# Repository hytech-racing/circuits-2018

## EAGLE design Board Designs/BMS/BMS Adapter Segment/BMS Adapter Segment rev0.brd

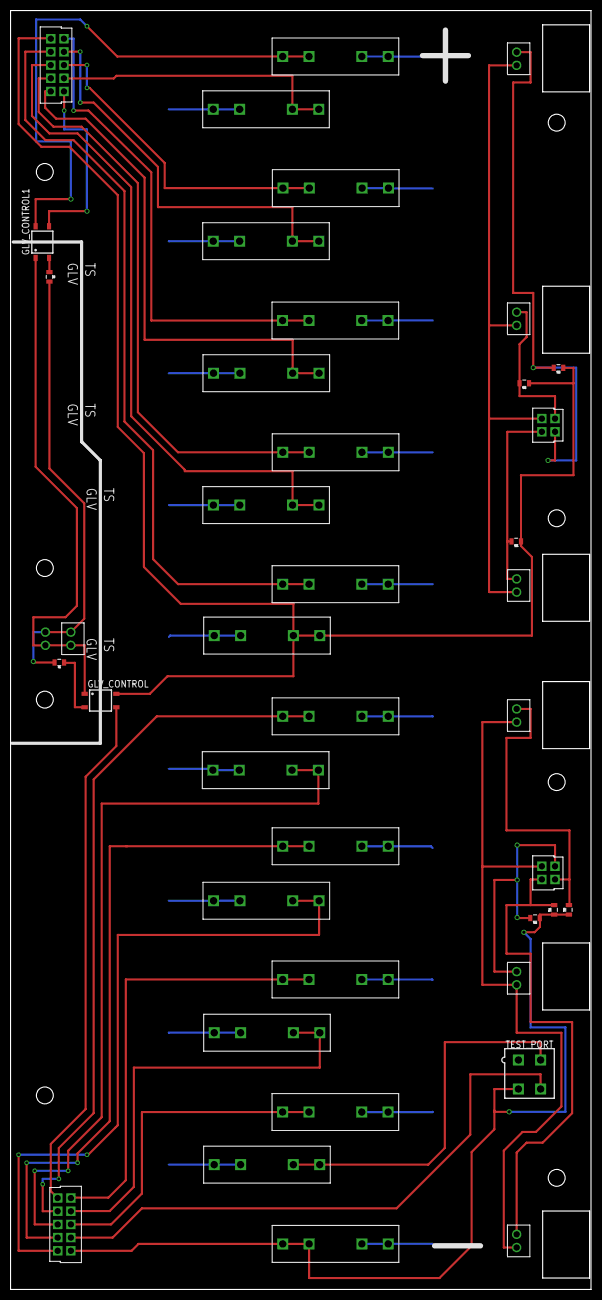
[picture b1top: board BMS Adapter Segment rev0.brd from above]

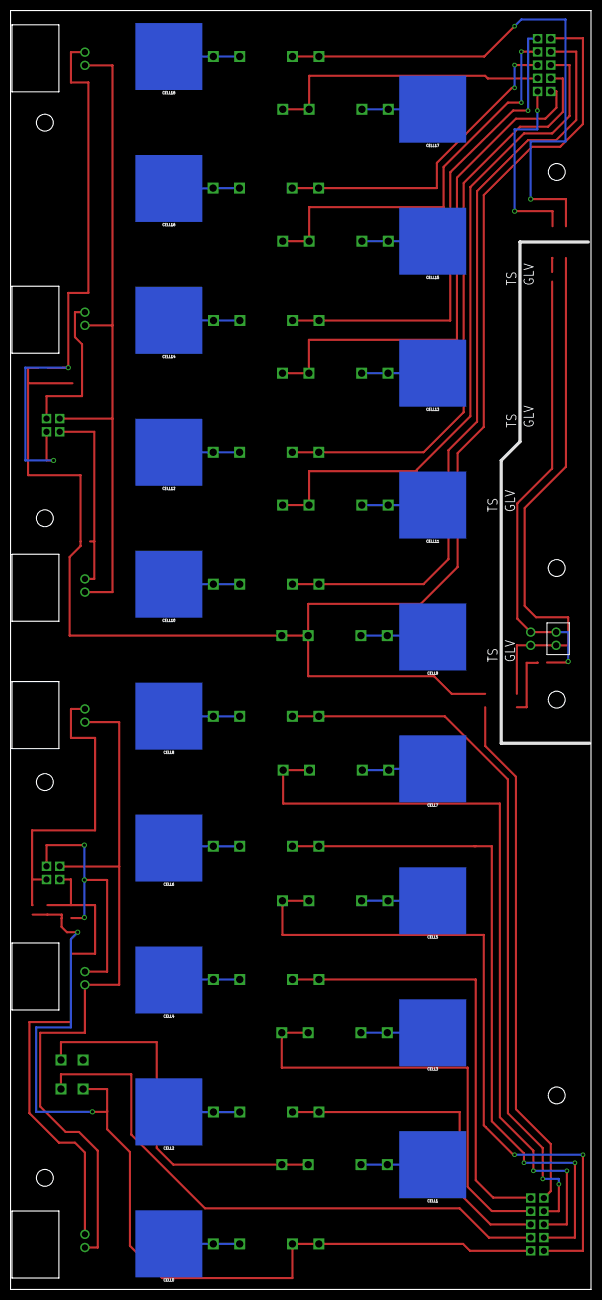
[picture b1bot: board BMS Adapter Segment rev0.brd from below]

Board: 2 copper layers, 110.0 x 242.4 mm, 61 parts (20 on the bottom side), 53 nets.

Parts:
CELL0, CELL1, CELL2, CELL3, CELL4, CELL5, CELL6, CELL7, CELL8, CELL9, CELL10, CELL11, CELL12, CELL13, CELL14, CELL15, CELL16, CELL17, CELL18: KEYSTONE5222
F0, F1, F2, F3, F4, F5, F6, F7, F8, F9, F10, F11, F12, F13, F14, F15, F16, F17, F18: 0751.0110
G1, G2: 2k; 0805
GLV_CONTROL, GLV_CONTROL1: CPC1002N; SOP04
TEST_PORT: MINIFIT_5566-4
TR1, TR2, TR3, TR4, TR5, TR6: 10kΩ; 0805
X1, X13: CONNECTOR-10NANO-FIT_VERTICAL_NO_CLIPS-10; NANO-FIT_VERTICAL_NO_CLIPS-10
X2, X3, X7, X8, X9, X10, X11, X12: CONNECTOR-2NANO-FIT_VERTICAL_NO_CLIPS-2; NANO-FIT_VERTICAL_NO_CLIPS-2
X5, X6: CONNECTOR-4NANO-FIT_VERTICAL_NO_CLIPS-4; NANO-FIT_VERTICAL_NO_CLIPS-4

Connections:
CC0: CELL0.P$1, F0.L1, F0.L2
CC1: CELL1.P$1, F1.L1, F1.L2
CC2: CELL2.P$1, F2.L1, F2.L2
CC3: CELL3.P$1, F3.L1, F3.L2
CC4: CELL4.P$1, F4.L1, F4.L2
CC5: CELL5.P$1, F5.L1, F5.L2
CC6: CELL6.P$1, F6.L1, F6.L2
CC7: CELL7.P$1, F7.L1, F7.L2
CC8: CELL8.P$1, F8.L1, F8.L2
CC9: CELL9.P$1, F9.L1, F9.L2
CC10: CELL10.P$1, F10.L1, F10.L2
CC11: CELL11.P$1, F11.L1, F11.L2
CC12: CELL12.P$1, F12.L1, F12.L2
CC13: CELL13.P$1, F13.L1, F13.L2
CC14: CELL14.P$1, F14.L1, F14.L2
CC15: CELL15.P$1, F15.L1, F15.L2
CC16: CELL16.P$1, F16.L1, F16.L2
CC17: CELL17.P$1, F17.L1, F17.L2
CC18: CELL18.P$1, F18.L1, F18.L2
GND: G1.2, G2.2, X2.P$2, X3.P$2
unnamed: GLV_CONTROL1.3, X1.P$10
unnamed: GLV_CONTROL.3, X13.P$10
SENSE0: F0.R1, F0.R2, TEST_PORT.3, TR1.1, TR2.1, TR3.1, X13.P$1
SENSE1: F1.R1, F1.R2, TEST_PORT.2
SENSE1_J: TEST_PORT.4, X13.P$2
SENSE2: F2.R1, F2.R2, X13.P$3
SENSE3: F3.R1, F3.R2, X13.P$4
SENSE4: F4.R1, F4.R2, X13.P$5
SENSE5: F5.R1, F5.R2, X13.P$6
SENSE6: F6.R1, F6.R2, X13.P$7
SENSE7: F7.R1, F7.R2, X13.P$8
SENSE8: F8.R1, F8.R2, X13.P$9
SENSE9: F9.R1, F9.R2, GLV_CONTROL.4, TR4.1, TR5.1, TR6.1, X1.P$1
SENSE10: F10.R1, F10.R2, X1.P$2
SENSE11: F11.R1, F11.R2, X1.P$3
SENSE12: F12.R1, F12.R2, X1.P$4
SENSE13: F13.R1, F13.R2, X1.P$5
SENSE14: F14.R1, F14.R2, X1.P$6
SENSE15: F15.R1, F15.R2, X1.P$7
SENSE16: F16.R1, F16.R2, X1.P$8
SENSE17: F17.R1, F17.R2, X1.P$9
SENSE18: F18.R1, F18.R2, GLV_CONTROL1.4
SSR-: G1.1, GLV_CONTROL.2
SSR-1: G2.1, GLV_CONTROL1.2
THERM1: TR1.2, X6.P$2, X7.P$2
THERM2: TR2.2, X6.P$3, X8.P$2
THERM3: TR3.2, X6.P$4, X9.P$2
THERM4: TR4.2, X5.P$2, X10.P$2
THERM5: TR5.2, X5.P$3, X11.P$2
THERM6: TR6.2, X5.P$4, X12.P$2
THERM_POWER_1: X6.P$1, X7.P$1, X8.P$1, X9.P$1
THERM_POWER_2: X5.P$1, X10.P$1, X11.P$1, X12.P$1
VCCINT: GLV_CONTROL.1, GLV_CONTROL1.1, X2.P$1, X3.P$1

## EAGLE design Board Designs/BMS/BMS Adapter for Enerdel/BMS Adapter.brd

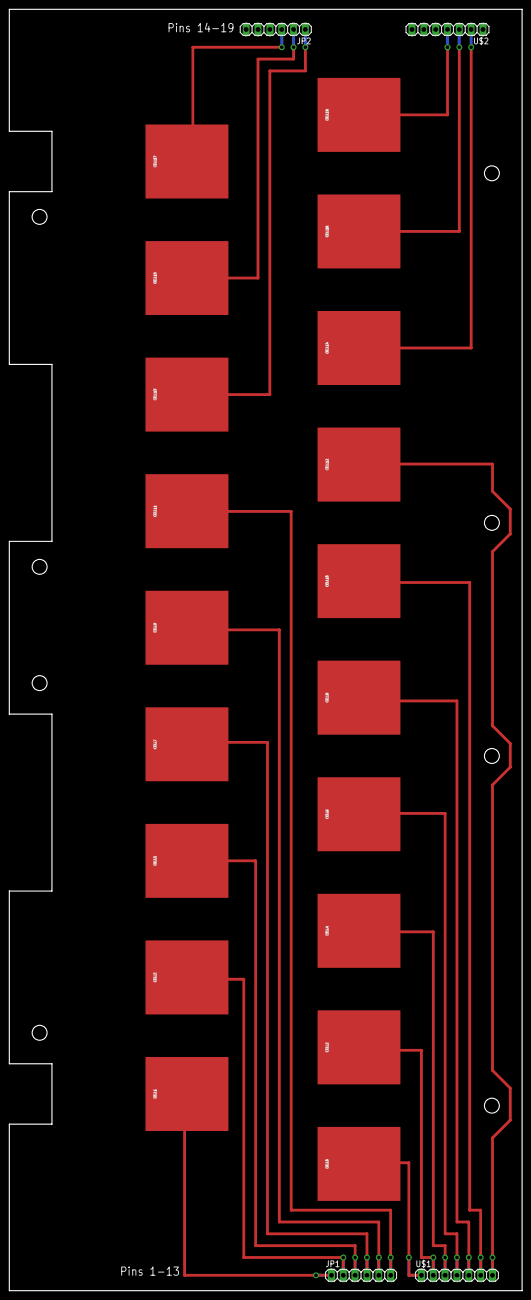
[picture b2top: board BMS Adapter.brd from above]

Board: 2 copper layers, 110.0 x 274.8 mm, 23 parts (0 on the bottom side), 19 nets.

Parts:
CELL0, CELL1, CELL2, CELL3, CELL4, CELL5, CELL6, CELL7, CELL8, CELL9, CELL10, CELL11, CELL12, CELL13, CELL14, CELL15, CELL16, CELL17, CELL18: BATTERY_SPRING_KEYSTONE5222; KEYSTONE5222
JP1, JP2: 1X06
U$1, U$2: M07; 1X07

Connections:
unnamed: CELL0.P$1, U$1.1
unnamed: CELL2.P$1, U$1.2
unnamed: CELL4.P$1, U$1.3
unnamed: CELL6.P$1, U$1.4
unnamed: CELL8.P$1, U$1.5
unnamed: CELL10.P$1, U$1.6
unnamed: CELL12.P$1, U$1.7
unnamed: CELL1.P$1, JP1.1
unnamed: CELL3.P$1, JP1.2
unnamed: CELL5.P$1, JP1.3
unnamed: CELL7.P$1, JP1.4
unnamed: CELL9.P$1, JP1.5
unnamed: CELL11.P$1, JP1.6
unnamed: CELL18.P$1, U$2.4
unnamed: CELL16.P$1, U$2.3
unnamed: CELL14.P$1, U$2.2
unnamed: CELL13.P$1, JP2.1
unnamed: CELL15.P$1, JP2.2
unnamed: CELL17.P$1, JP2.3

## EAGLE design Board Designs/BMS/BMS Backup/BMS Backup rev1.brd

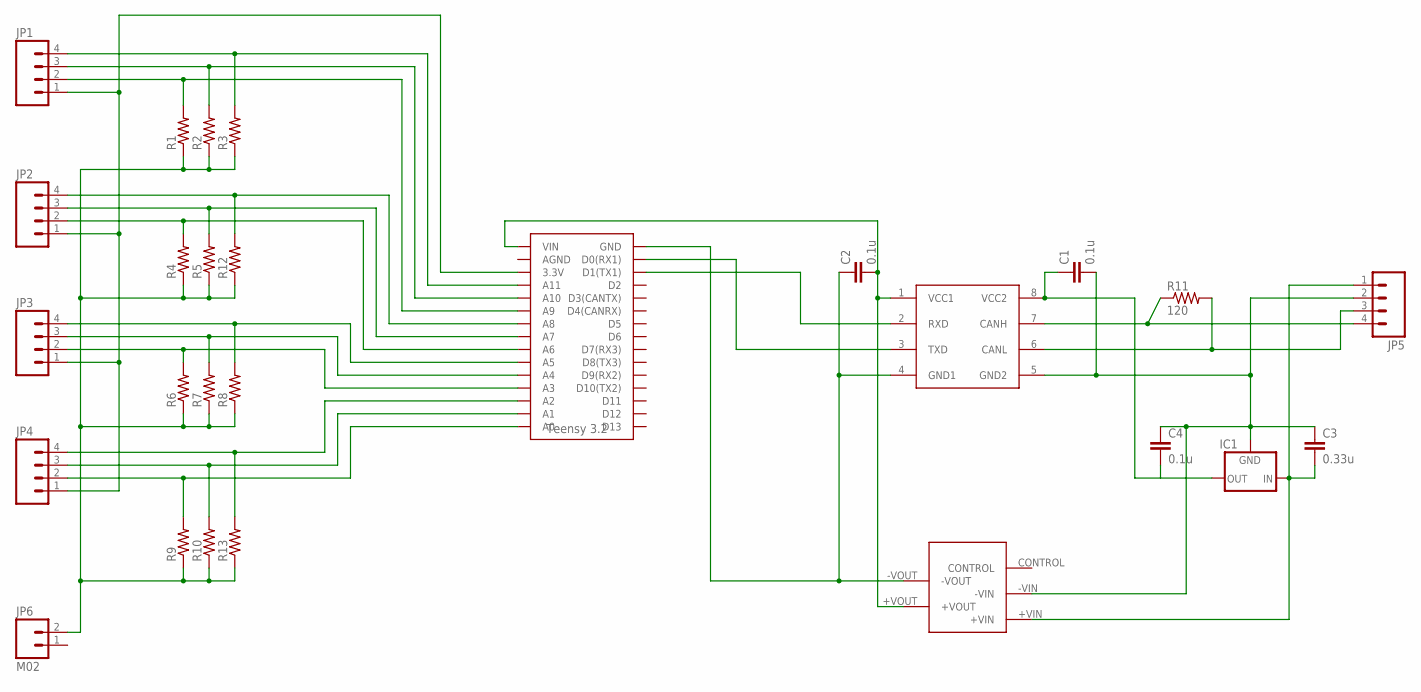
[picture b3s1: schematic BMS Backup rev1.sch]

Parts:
C1, C2, C4: 0.1u; 0805
C3: 0.33u; 0805
IC1: 5VREG_L7805SPACED; TO-220-SPACED
JP1, JP2, JP3, JP4, JP5: M04; 1X04
JP6: M02; 1X02
R1, R2, R3, R4, R5, R6, R7, R8, R9, R10, R12, R13: RESISTOR0805-RES; 0805
R11: 120; 0805
U$1: TEENSY_3.2_12ANALOG
U$2: ISO1050CAN; SOIC-08
U$3: NCS1S1205SC-12V-5VCONVERTER; DCDC-CONVERTER

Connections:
3.3V: JP1.1, JP2.1, JP3.1, JP4.1, U$1.3.3V
unnamed: C1.2, C3.1, C4.1, IC1.2 (GND), JP5.2, U$2.5 (GND2), U$3.-VIN
unnamed: JP3.3, R7.2, U$1.A4
unnamed: JP3.4, R8.2, U$1.A5
unnamed: C3.2, IC1.1 (IN), JP5.1, U$3.+VIN
unnamed: C1.1, C4.2, IC1.3 (OUT), U$2.8 (VCC2)
unnamed: JP5.4, R11.1, U$2.7 (CANH)
unnamed: JP5.3, R11.2, U$2.6 (CANL)
unnamed: U$1.D0(RX1), U$2.3 (TXD)
unnamed: U$1.D1(TX1), U$2.2 (RXD)
unnamed: C2.2, U$1.VIN, U$2.1 (VCC1), U$3.+VOUT
unnamed: C2.1, U$1.GND, U$2.4 (GND1), U$3.-VOUT
unnamed: JP2.4, R12.2, U$1.A8
unnamed: JP4.4, R13.2, U$1.A2
THERM1: JP1.2, R1.2, U$1.A9
THERM2: JP1.3, R2.2, U$1.A10
THERM3: JP1.4, R3.2, U$1.A11
THERM4: JP2.2, R4.2, U$1.A6
THERM5: JP2.3, R5.2, U$1.A7
THERM6: JP3.2, R6.2, U$1.A3
THERM9: JP4.2, R9.2, U$1.A0
THERM10: JP4.3, R10.2, U$1.A1
TS_GND: JP6.2, R1.1, R2.1, R3.1, R4.1, R5.1, R6.1, R7.1, R8.1, R9.1, R10.1, R12.1, R13.1

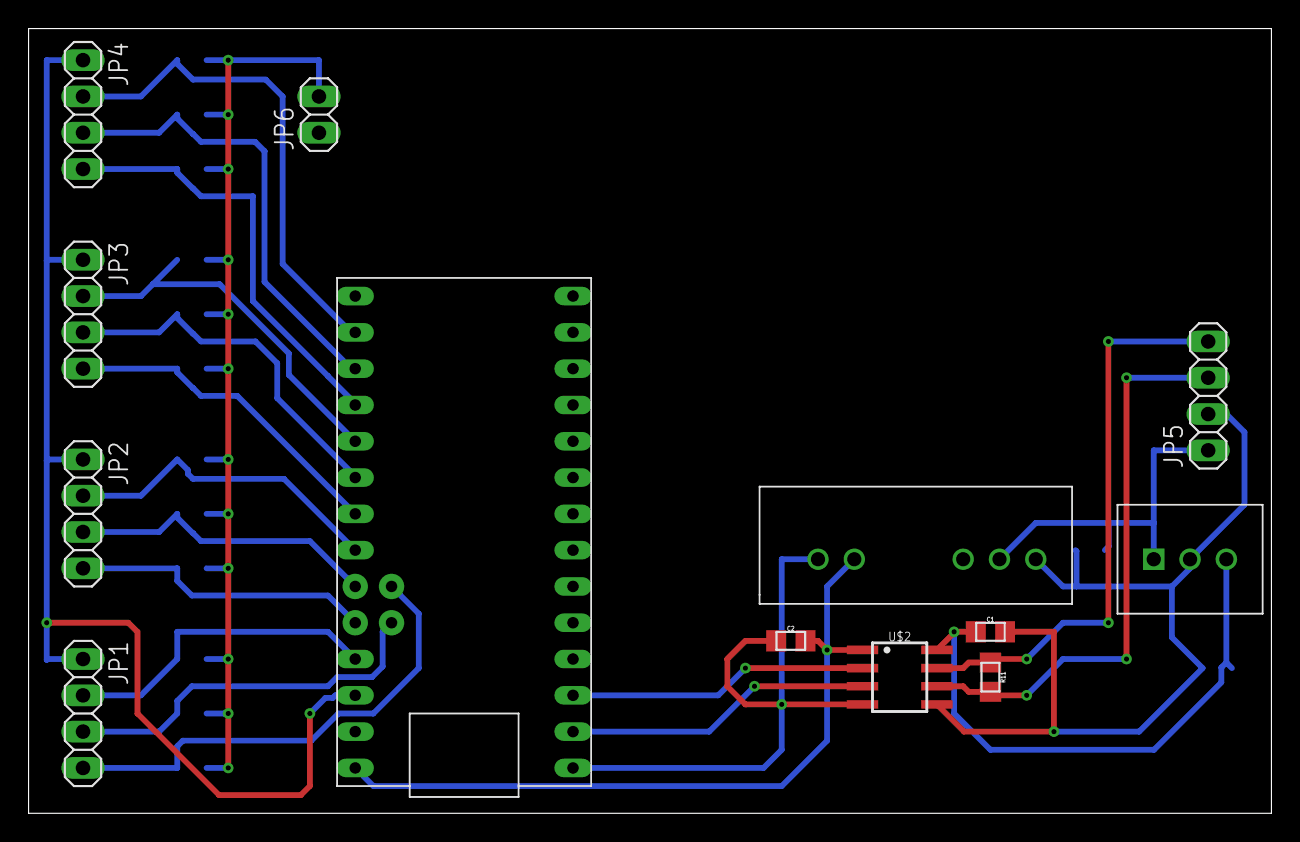
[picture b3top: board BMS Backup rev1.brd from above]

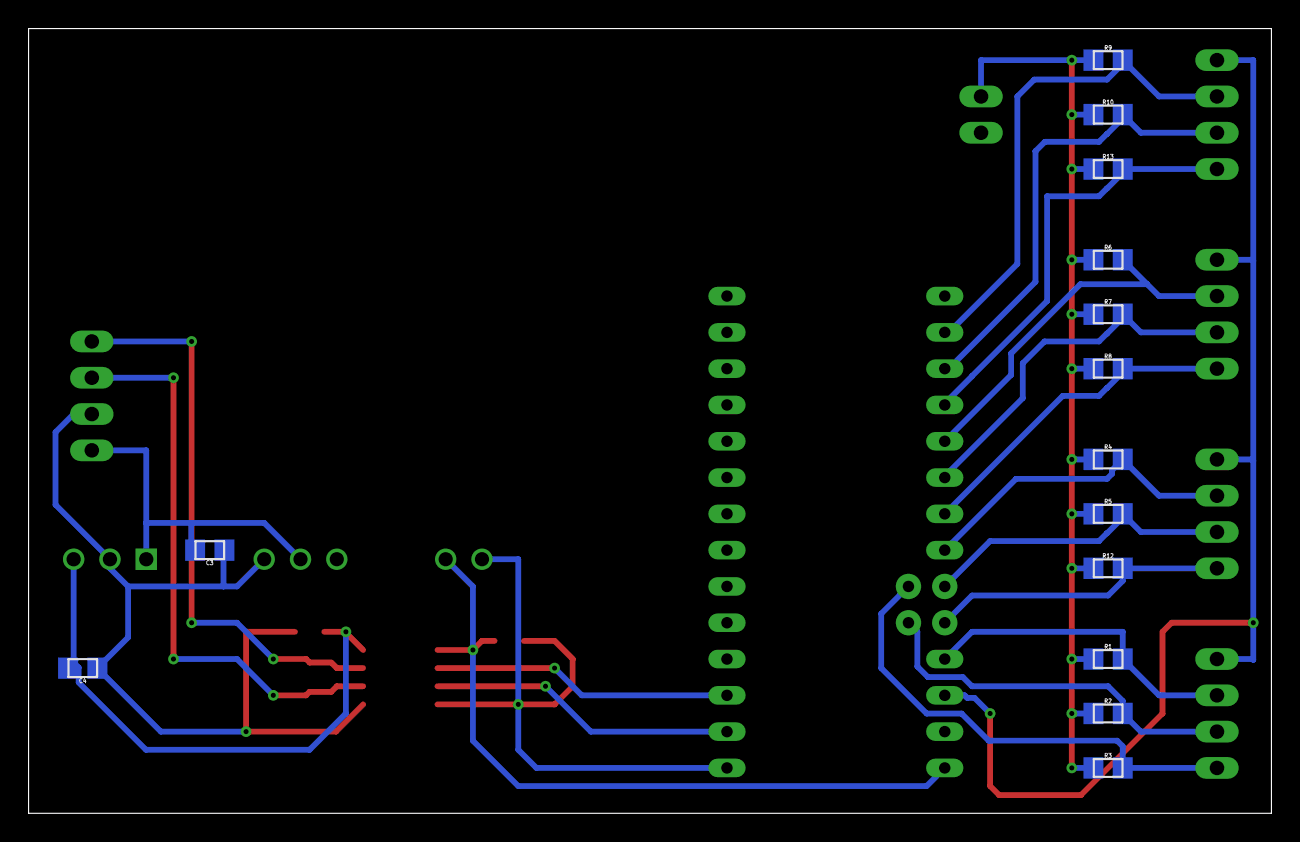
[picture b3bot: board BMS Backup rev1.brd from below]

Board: 2 copper layers, 87.0 x 54.9 mm, 27 parts (14 on the bottom side), 23 nets.

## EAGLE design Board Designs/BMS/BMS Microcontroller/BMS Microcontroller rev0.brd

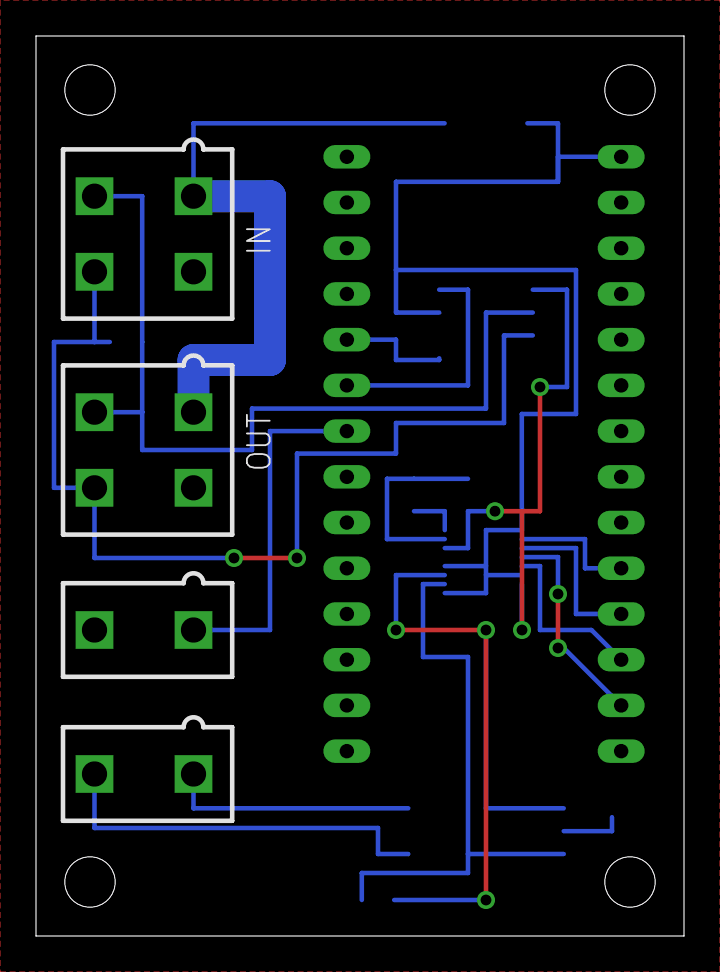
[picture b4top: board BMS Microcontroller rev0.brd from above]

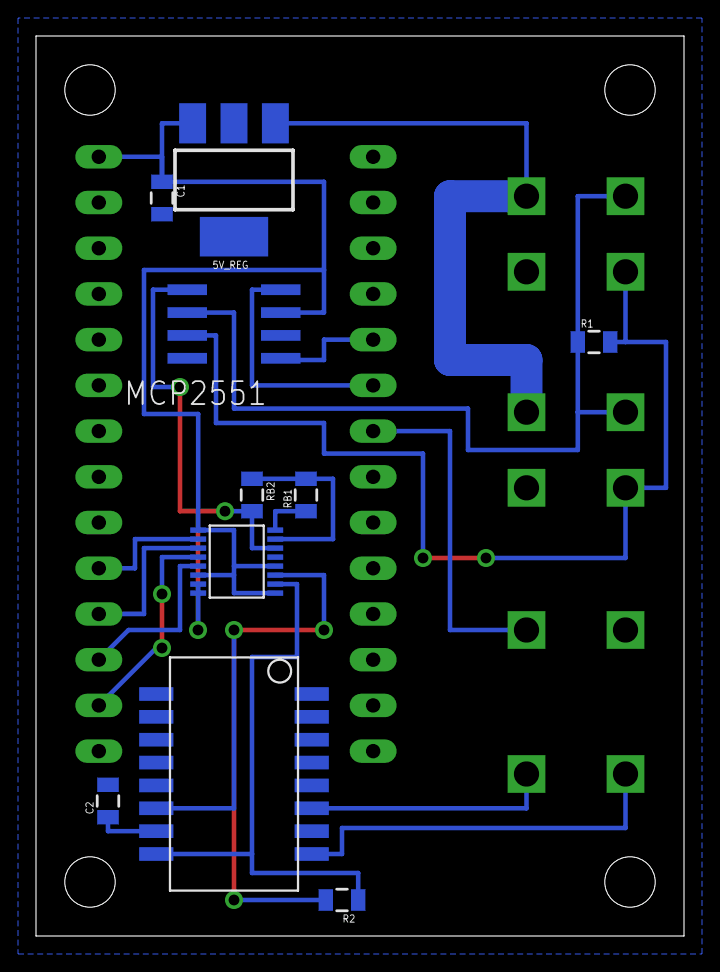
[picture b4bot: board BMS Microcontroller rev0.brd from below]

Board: 2 copper layers, 36.0 x 50.0 mm, 15 parts (10 on the bottom side), 19 nets.

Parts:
5V_REG: SOT223
BMS_OK_SIGNAL: MINIFIT_5566-2
C1: 0.1uF; 0805
C2: 100pF; 0805
IN: MINIFIT_5566-4
ISOSPI: MINIFIT_5566-2
MCP2551: MCP2551; SOIC-08
OUT: MINIFIT_5566-4
R1: 120Ω; 0805
R2: 120Ω; 0805
RB1, RB2: 0805
TRANSFORMER-: 749010013
U$1: LTC6820
U$3: TEENSY_3.2_SIMPLE

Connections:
5V_SUPPLY: 5V_REG.3, C1.1, MCP2551.3, U$1.1, U$1.6, U$1.9, U$1.12, U$3.VIN
12V_SUPPLY: 5V_REG.1, IN.1, OUT.1
CANH: IN.4, MCP2551.7, OUT.4, R1.2
CANL: IN.3, MCP2551.6, OUT.3, R1.1
GND: 5V_REG.2, 5V_REG.4, C1.2, C2.2, IN.2, MCP2551.2, MCP2551.5, OUT.2, RB2.2, U$1.7, U$1.8, U$1.13, U$1.14, U$3.AGND, U$3.GND
ISOSPI-M: ISOSPI.2, TRANSFORMER-.8
ISOSPI-P: ISOSPI.1, TRANSFORMER-.6
unnamed: U$1.5, U$3.A1
unnamed: U$1.4, U$3.A0
unnamed: U$1.3, U$3.A2
unnamed: U$1.2, U$3.A3
unnamed: C2.1, TRANSFORMER-.10
unnamed: RB1.1, U$1.16
unnamed: RB1.2, RB2.1, U$1.15
unnamed: R2.2, TRANSFORMER-.11, U$1.11
unnamed: R2.1, TRANSFORMER-.9, U$1.10
unnamed: BMS_OK_SIGNAL.1, U$3.D5
RX: MCP2551.4, U$3.D4(CANRX)
TX: MCP2551.1, U$3.D3(CANTX)

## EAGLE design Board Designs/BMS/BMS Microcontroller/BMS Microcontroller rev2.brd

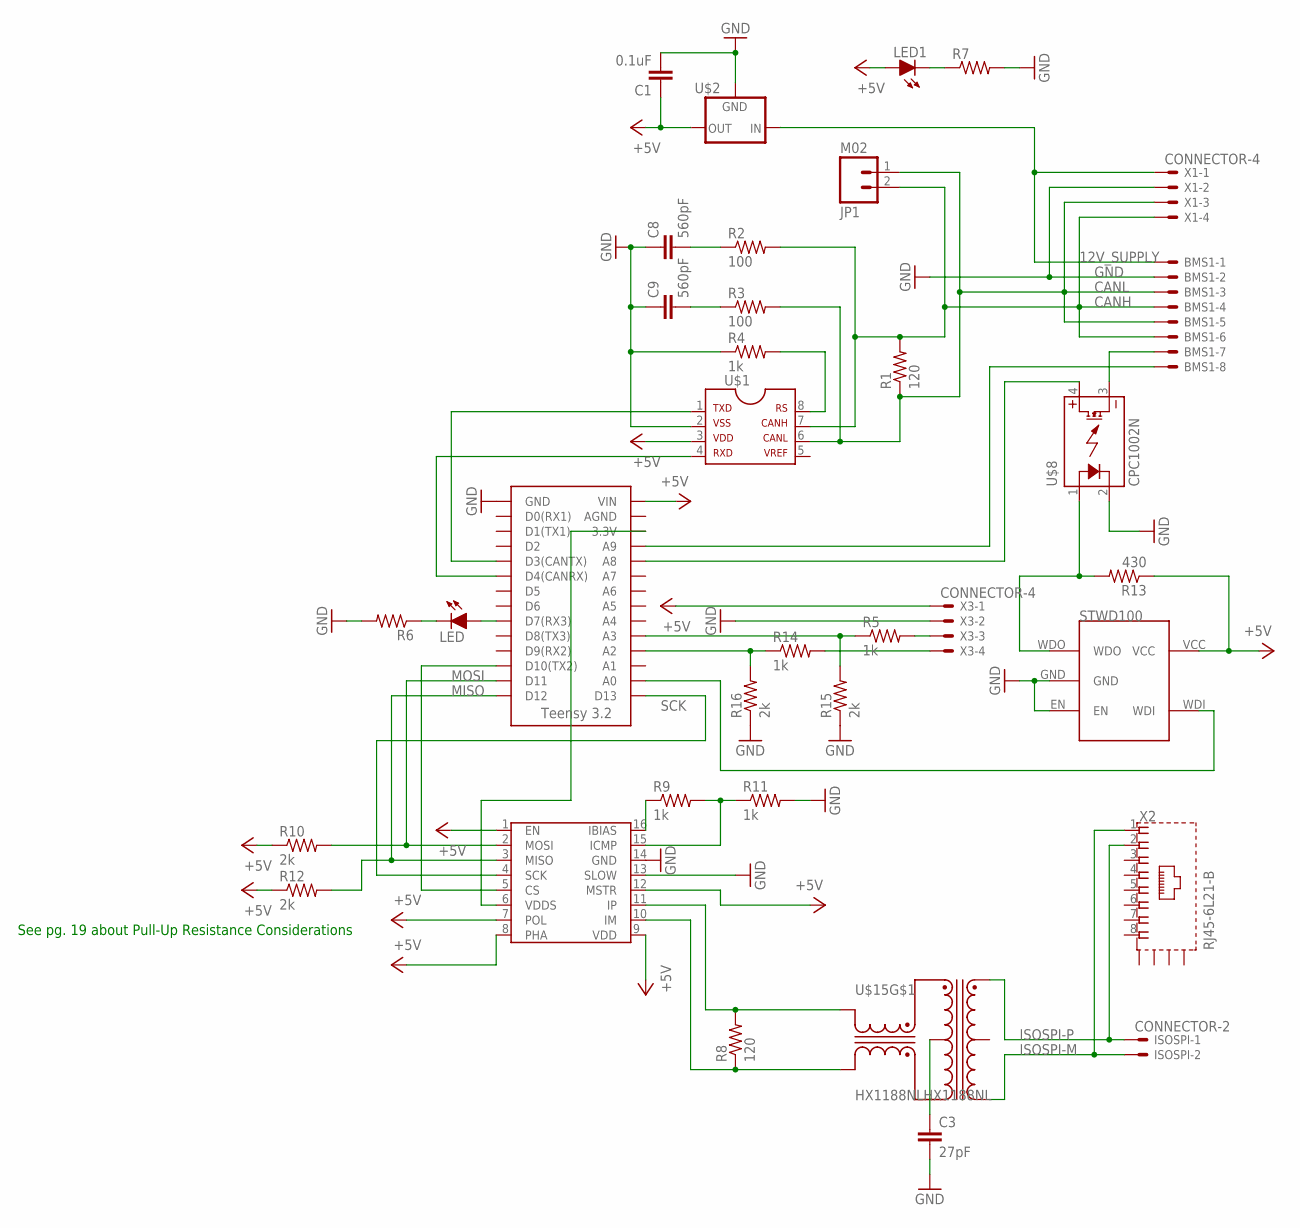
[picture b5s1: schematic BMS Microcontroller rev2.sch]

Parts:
BMS1: MINIFIT_5566-8
C1: 0.1uF; 0805
C3: 27pF; 0805
C8, C9: 560pF; 0805
ISOSPI: CONNECTOR-2; MINIFIT_5566-2
JP1: M02; 1X02
LED, LED1: LED-0805; LED-805
R1, R8: 120; 0805
R2, R3: 100; 0805
R4, R5, R9, R11, R14: 1k; 0805
R6, R7: RESISTOR0805-RES; 0805
R10, R12, R15, R16: 2k; 0805
R13: 430; 0805
U$1: MCP2551; SOIC-08
U$2: 5VREG_LM340-NLM340MPX-5.0/NOPB; SOT223
U$3: STWD100; SOT23-5
U$6: LTC6820; MSOP-16
U$7: TEENSY_3.2_SIMPLE
U$8: CPC1002N; SOP04
U$15: HX1188NLHX1188NL; HX1188NL
X1, X3: CONNECTOR-4; MINIFIT_5566-4
X2: RJ45-6L21-B; RJ45-SHIELD1

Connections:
12V_SUPPLY: BMS1.1, U$2.1 (IN), X1.1
+5V: C1.1, LED1.A, R10.1, R12.1, R13.1, U$1.3, U$2.3 (OUT), U$3.VCC, U$6.1 (EN), U$6.7 (POL), U$6.8 (PHA), U$6.9 (VDD), U$6.12 (MSTR), U$7.VIN, X3.1
CANH: BMS1.4, BMS1.6, JP1.2, R1.2, R2.2, U$1.7, X1.4
CANL: BMS1.3, BMS1.5, JP1.1, R1.1, R3.2, U$1.6, X1.3
GND: BMS1.2, C1.2, C3.2, C8.1, C9.1, R4.1, R6.2, R7.2, R11.2, R15.1, R16.1, U$1.2, U$2.2 (GND), U$2.4 (GND), U$3.EN, U$3.GND, U$6.13 (SLOW), U$6.14 (GND), U$7.GND, U$8.2 (CONTROL-), X1.2, X3.2
ISOSPI-M: ISOSPI.2, U$15.3 (D-), X2.1
ISOSPI-P: ISOSPI.1, U$15.1 (D+), X2.2
MISO: R12.2, U$6.3 (MISO), U$7.D12
MOSI: R10.2, U$6.2 (MOSI), U$7.D11
unnamed: R5.2, X3.3
unnamed: U$1.4, U$7.D4(CANRX)
unnamed: LED.A, U$7.D7(RX3)
unnamed: U$6.6 (VDDS), U$7.3.3V
unnamed: R5.1, R15.2, U$7.A3
unnamed: R14.2, X3.4
unnamed: BMS1.7, U$8.3 (DC-)
unnamed: R14.1, R16.2, U$7.A2
unnamed: U$3.WDI, U$7.A0
unnamed: R13.2, U$3.WDO, U$8.1 (CONTROL+)
unnamed: U$7.A8, U$8.4 (DC+)
unnamed: U$1.1, U$7.D3(CANTX)
unnamed: BMS1.8, U$7.A9
unnamed: C8.2, R2.1
unnamed: U$6.5 (CS), U$7.D10(TX2)
unnamed: R4.2, U$1.8
unnamed: C9.2, R3.1
unnamed: LED.C, R6.1
unnamed: LED1.C, R7.1
unnamed: R9.1, U$6.16 (IBIAS)
unnamed: R9.2, R11.1, U$6.15 (ICMP)
unnamed: R8.1, U$6.10 (IM), U$15.14 (X-)
unnamed: R8.2, U$6.11 (IP), U$15.16 (X+)
unnamed: C3.1, U$15.15 (CX)
SCK: U$6.4 (SCK), U$7.D13

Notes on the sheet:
See pg. 19 about Pull-Up Resistance Considerations

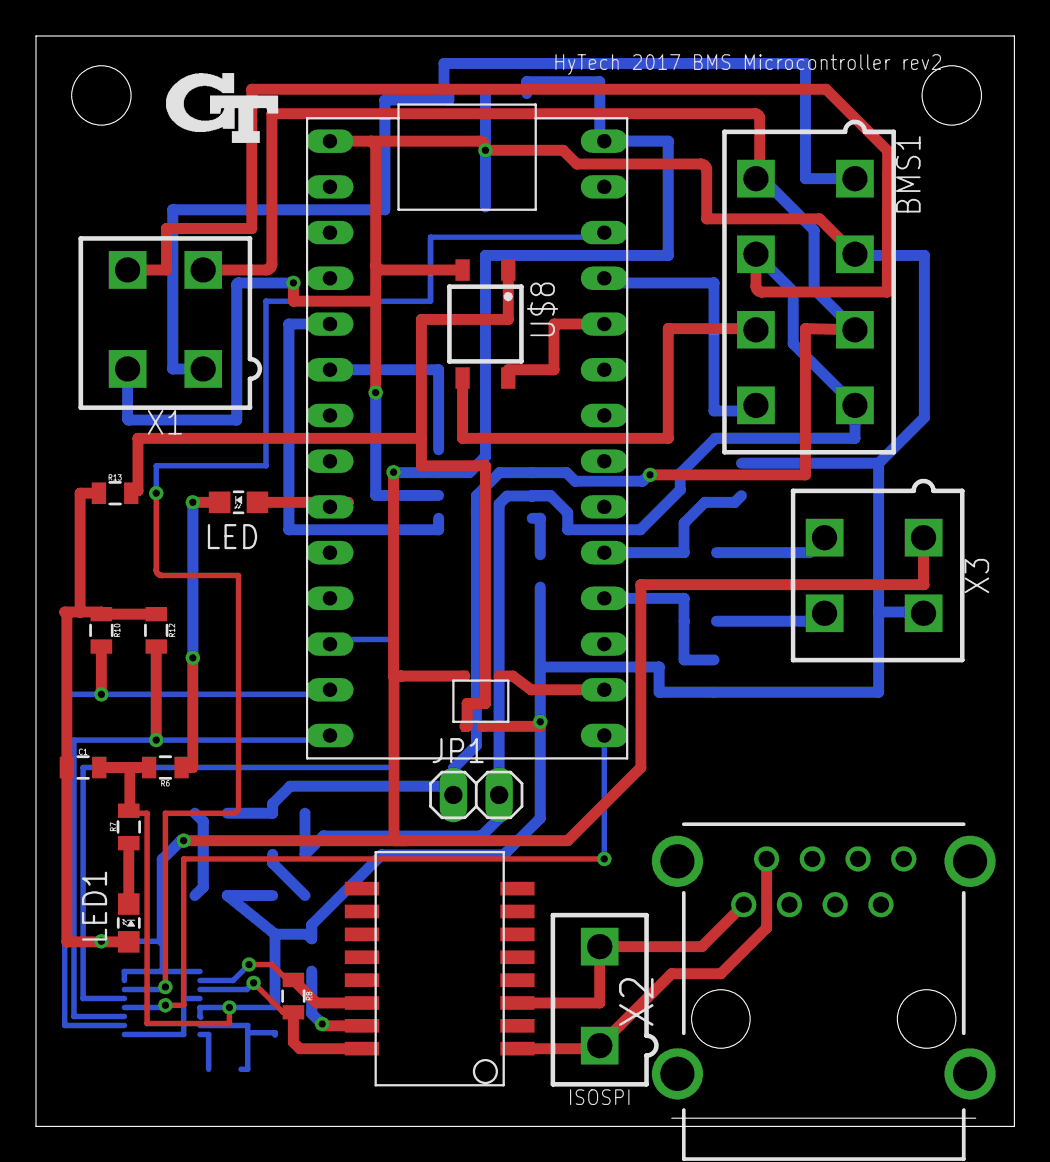
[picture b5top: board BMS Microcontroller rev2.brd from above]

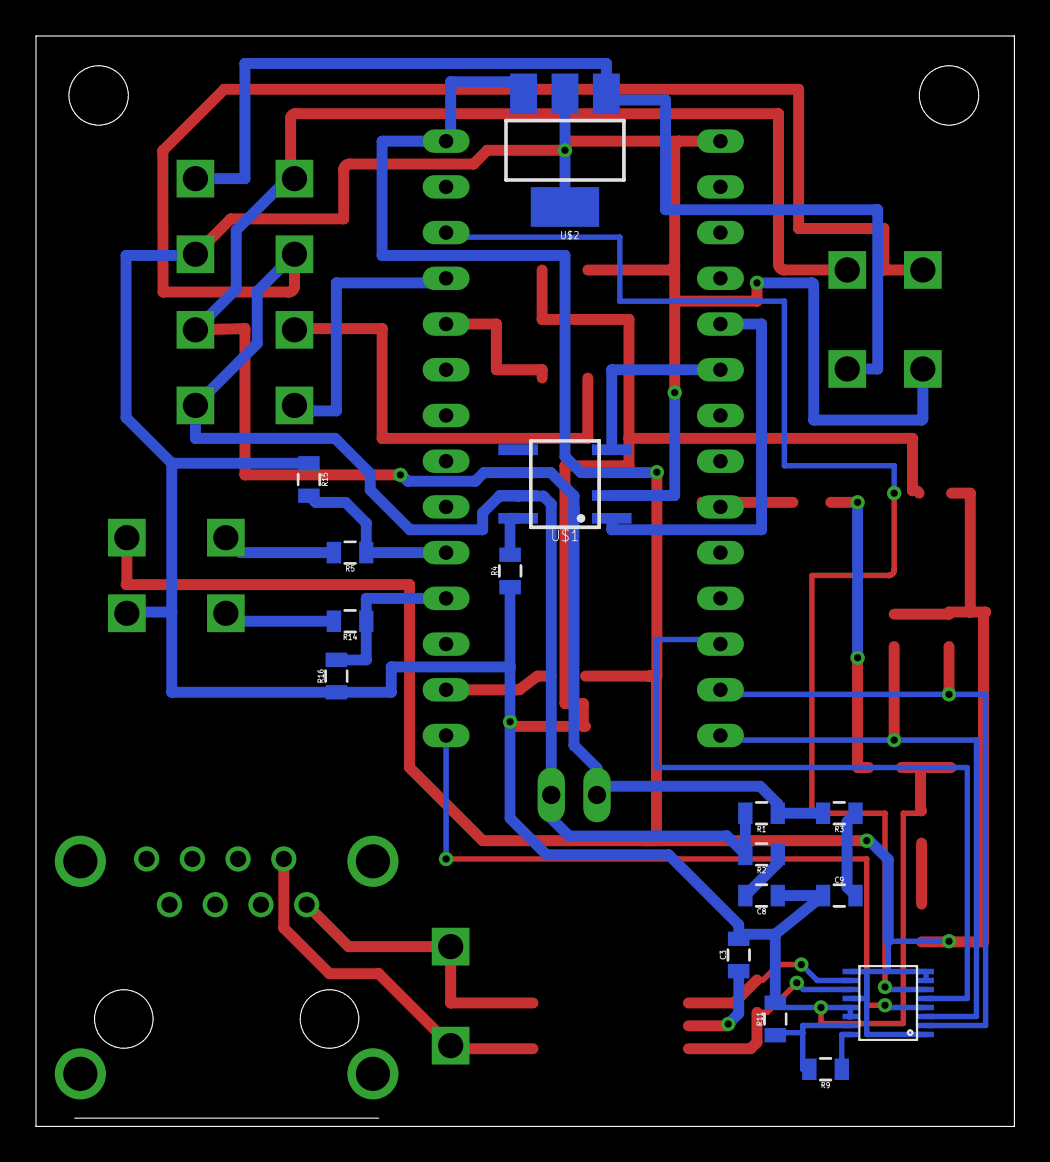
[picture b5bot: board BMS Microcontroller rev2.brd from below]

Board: 2 copper layers, 54.3 x 60.6 mm, 35 parts (16 on the bottom side), 34 nets.

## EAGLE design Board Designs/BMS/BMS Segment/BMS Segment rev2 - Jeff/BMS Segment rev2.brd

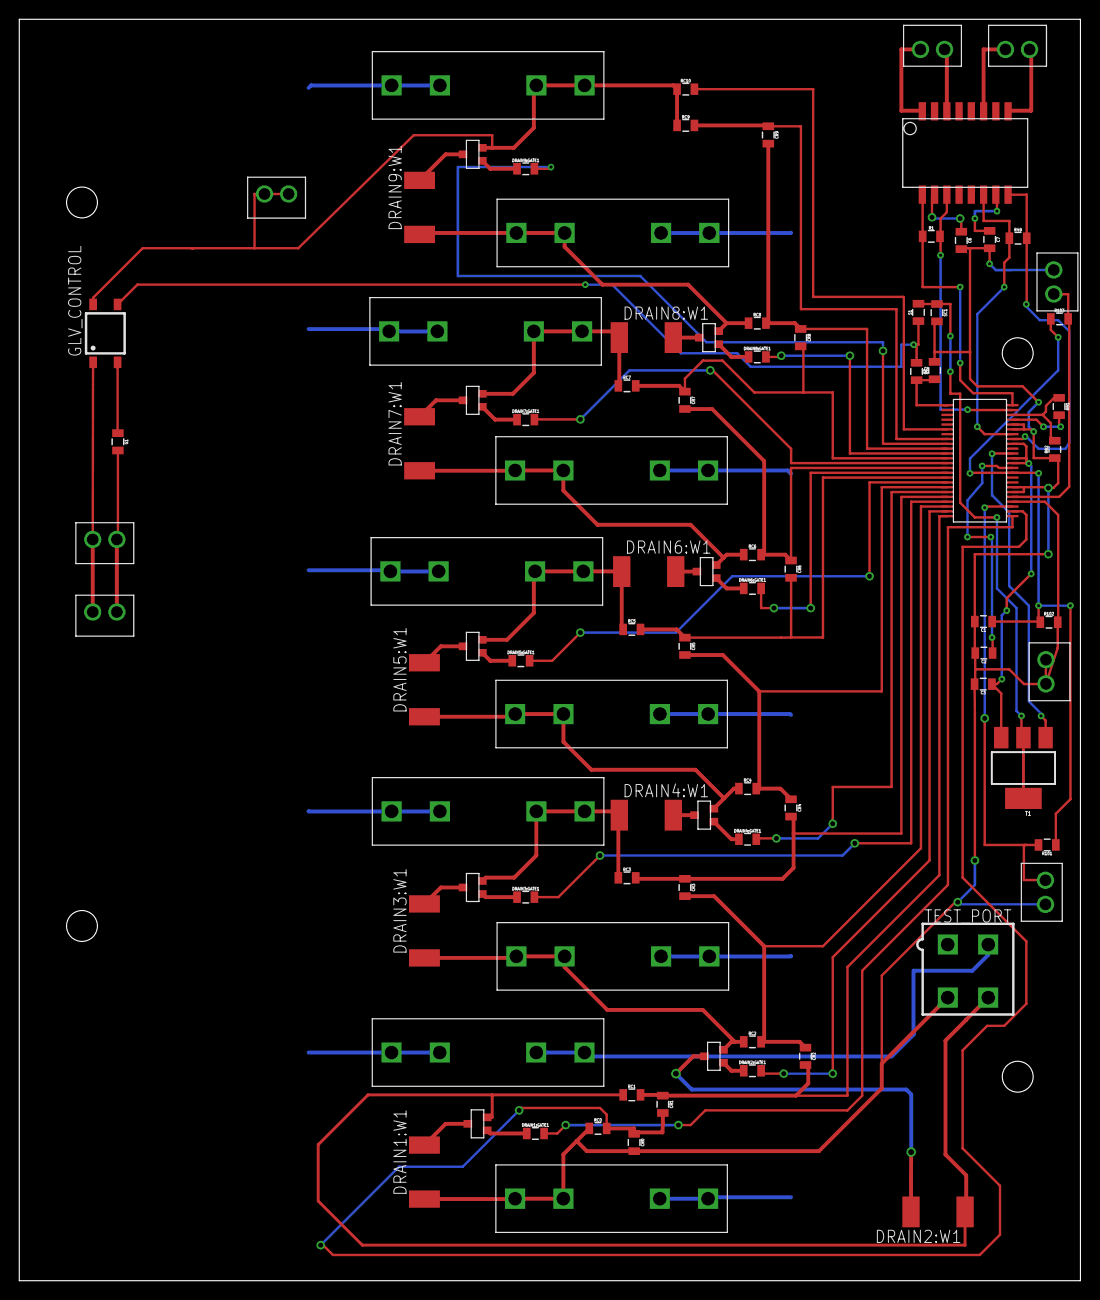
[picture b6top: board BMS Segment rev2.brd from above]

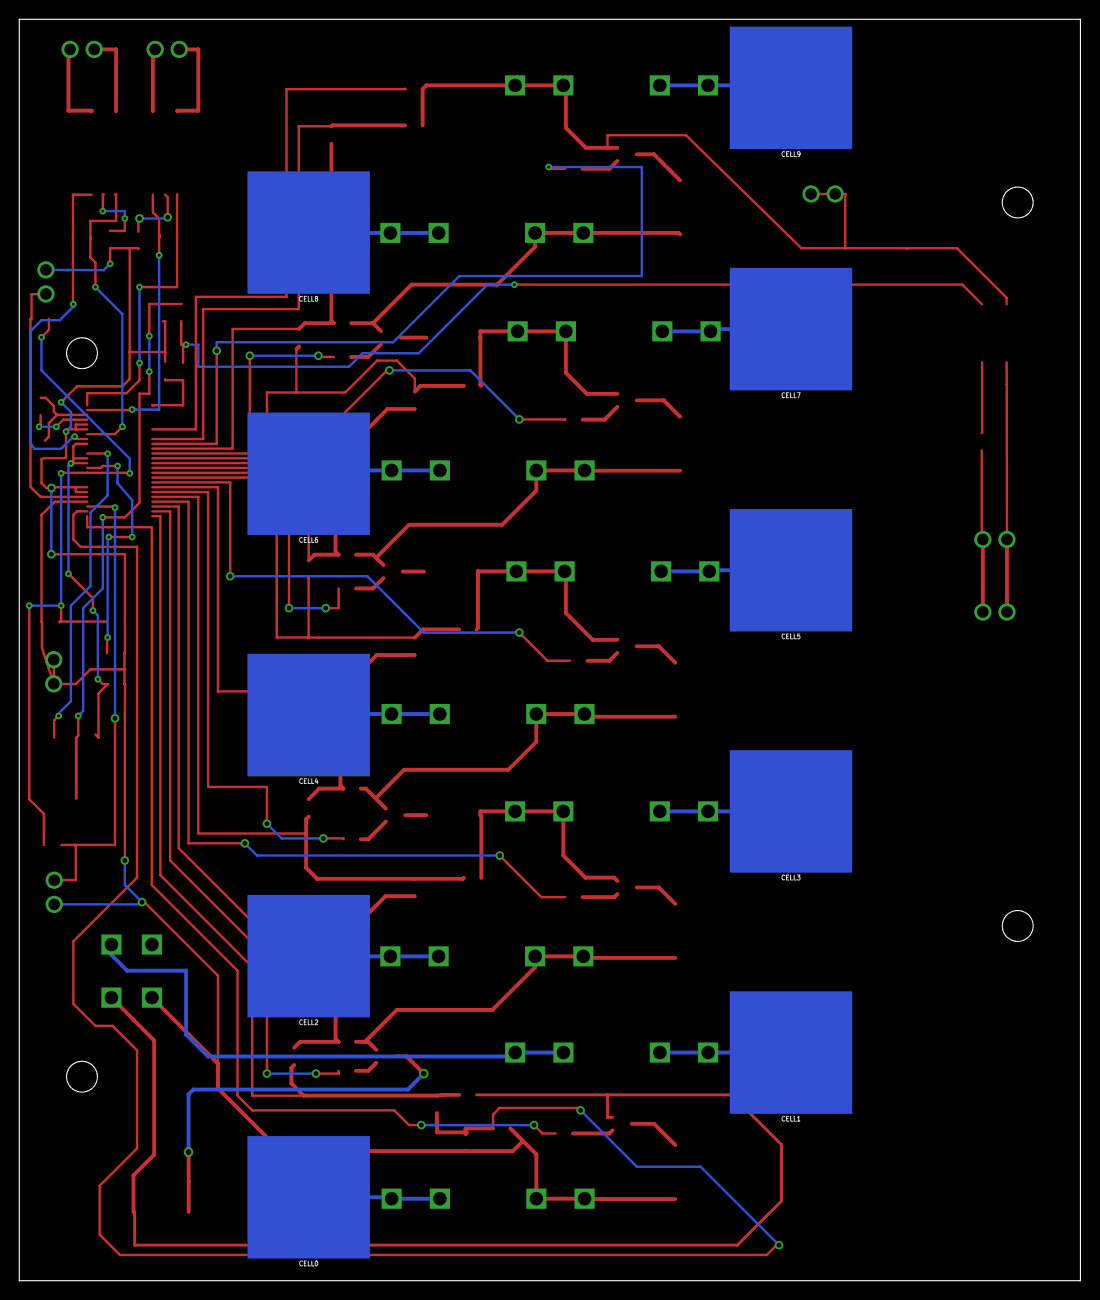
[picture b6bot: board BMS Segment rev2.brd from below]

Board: 2 copper layers, 110.0 x 130.8 mm, 98 parts (10 on the bottom side), 84 nets.

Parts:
C1, C2, C3: 1uF; 0805
C6, C7: 25pF; 0805
CELL0, CELL1, CELL2, CELL3, CELL4, CELL5, CELL6, CELL7, CELL8, CELL9: KEYSTONE5222
CR0, CR1, CR2, CR3, CR4, CR5, CR6, CR7, CR8, CR9: 10nF; 0805
DRAIN1:GATE1, DRAIN2:GATE1, DRAIN3:GATE1, DRAIN4:GATE1, DRAIN5:GATE1, DRAIN6:GATE1, DRAIN7:GATE1, DRAIN8:GATE1, DRAIN9:GATE1: 3.3kΩ; 0805
DRAIN1:PFET1, DRAIN2:PFET1, DRAIN3:PFET1, DRAIN4:PFET1, DRAIN5:PFET1, DRAIN6:PFET1, DRAIN7:PFET1, DRAIN8:PFET1, DRAIN9:PFET1: P-CHANNEL_MOSFET_DMP3099L-7; SOT23
DRAIN1:W1, DRAIN2:W1, DRAIN3:W1, DRAIN4:W1, DRAIN5:W1, DRAIN6:W1, DRAIN7:W1, DRAIN8:W1, DRAIN9:W1: 33Ω; R2512
F0, F1, F2, F3, F4, F5, F6, F7, F8, F9: 0751.0110
G1: 100Ω; 0805
GLV_CONTROL: CPC1002N; SOP04
R1, R49: 120Ω; 0805
R101, R102, R103: 10kΩ; 0805
RB1, RB2: 1.2k; 0805
RC0, RC1, RC2, RC3, RC4, RC5, RC6, RC7, RC8, RC9, RC10: 100Ω; 0805
S1, S2: 100Ω; 0805
SC1, SC2: 0.1uF; 0805
T1: NPN_BCP56T1; SOT223
TEST_PORT: MINIFIT_5566-4
TO_TOP: CONNECTOR-2NANO-FIT_VERTICAL-2; NANO-FIT_VERTICAL-2
TRANSFORMER-: 350uH; 749010013
U$2: LTC6804
X1, X2, X6, X7: CONNECTOR-2NANO-FIT_VERTICAL-2; NANO-FIT_VERTICAL-2
X3: Th1; NANO-FIT_VERTICAL-2
X4: Th2; NANO-FIT_VERTICAL-2
X5: Th3; NANO-FIT_VERTICAL-2

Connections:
C0: CR0.1, CR1.2, RC0.2, U$2.26
C1: CR1.1, CR2.2, RC1.2, U$2.24
C2: CR2.1, CR3.2, RC2.2, U$2.22
C3: CR3.1, CR4.2, RC3.2, U$2.20
C4: CR4.1, CR5.2, RC4.2, U$2.18
C5: CR5.1, CR6.2, RC5.2, U$2.16
C6: CR6.1, CR7.2, RC6.2, U$2.14
C7: CR7.1, CR8.2, RC7.2, U$2.12
C8: CR8.1, CR9.2, RC8.2, U$2.10
C9: CR9.1, RC9.2, U$2.8
C10: RC10.2, U$2.6
CC0: CELL0.P$1, F0.L1, F0.L2
CC1: CELL1.P$1, F1.L1, F1.L2
CC2: CELL2.P$1, F2.L1, F2.L2
CC3: CELL3.P$1, F3.L1, F3.L2
CC4: CELL4.P$1, F4.L1, F4.L2
CC5: CELL5.P$1, F5.L1, F5.L2
CC6: CELL6.P$1, F6.L1, F6.L2
CC7: CELL7.P$1, F7.L1, F7.L2
CC8: CELL8.P$1, F8.L1, F8.L2
CC9: CELL9.P$1, F9.L1, F9.L2
DRAIN1:DRAIN: DRAIN1:PFET1.3, DRAIN1:W1.2
DRAIN1:GATE: DRAIN1:GATE1.1, DRAIN1:PFET1.1
DRAIN2:DRAIN: DRAIN2:PFET1.3, DRAIN2:W1.2
DRAIN2:GATE: DRAIN2:GATE1.1, DRAIN2:PFET1.1
DRAIN3:DRAIN: DRAIN3:PFET1.3, DRAIN3:W1.2
DRAIN3:GATE: DRAIN3:GATE1.1, DRAIN3:PFET1.1
DRAIN4:DRAIN: DRAIN4:PFET1.3, DRAIN4:W1.2
DRAIN4:GATE: DRAIN4:GATE1.1, DRAIN4:PFET1.1
DRAIN5:DRAIN: DRAIN5:PFET1.3, DRAIN5:W1.2
DRAIN5:GATE: DRAIN5:GATE1.1, DRAIN5:PFET1.1
DRAIN6:DRAIN: DRAIN6:PFET1.3, DRAIN6:W1.2
DRAIN6:GATE: DRAIN6:GATE1.1, DRAIN6:PFET1.1
DRAIN7:DRAIN: DRAIN7:PFET1.3, DRAIN7:W1.2
DRAIN7:GATE: DRAIN7:GATE1.1, DRAIN7:PFET1.1
DRAIN8:DRAIN: DRAIN8:PFET1.3, DRAIN8:W1.2
DRAIN8:GATE: DRAIN8:GATE1.1, DRAIN8:PFET1.1
DRAIN9:DRAIN: DRAIN9:PFET1.3, DRAIN9:W1.2
DRAIN9:GATE: DRAIN9:GATE1.1, DRAIN9:PFET1.1
DRIVE: T1.1, U$2.38
GND: G1.2, X6.1, X7.1
ISOSPI-M_IN: TRANSFORMER-.8, X1.2
ISOSPI-M_OUT: TRANSFORMER-.3, X2.2
ISOSPI-P_IN: TRANSFORMER-.6, X1.1
ISOSPI-P_OUT: TRANSFORMER-.1, X2.1
unnamed: C7.1, TRANSFORMER-.10
unnamed: C6.1, TRANSFORMER-.15
unnamed: RB1.2, U$2.45
unnamed: R1.1, TRANSFORMER-.16, U$2.48
unnamed: RB1.1, RB2.2, U$2.46
unnamed: R49.1, TRANSFORMER-.11, U$2.42
unnamed: R49.2, TRANSFORMER-.9, U$2.41
unnamed: R1.2, TRANSFORMER-.14, U$2.47
S1: DRAIN1:GATE1.2, U$2.25
S2: DRAIN2:GATE1.2, U$2.23
S3: DRAIN3:GATE1.2, U$2.21
S4: DRAIN4:GATE1.2, U$2.19
S5: DRAIN5:GATE1.2, U$2.17
S6: DRAIN6:GATE1.2, U$2.15
S7: DRAIN7:GATE1.2, U$2.13
S8: DRAIN8:GATE1.2, U$2.11
S9: DRAIN9:GATE1.2, U$2.9
SENSE1: F1.R1, F1.R2, TEST_PORT.2
SENSE1_J: DRAIN1:PFET1.2, DRAIN2:W1.1, RC1.1, TEST_PORT.4
SENSE2: DRAIN2:PFET1.2, DRAIN3:W1.1, F2.R1, F2.R2, RC2.1
SENSE3: DRAIN3:PFET1.2, DRAIN4:W1.1, F3.R1, F3.R2, RC3.1
SENSE4: DRAIN4:PFET1.2, DRAIN5:W1.1, F4.R1, F4.R2, RC4.1
SENSE5: DRAIN5:PFET1.2, DRAIN6:W1.1, F5.R1, F5.R2, RC5.1
SENSE6: DRAIN6:PFET1.2, DRAIN7:W1.1, F6.R1, F6.R2, RC6.1
SENSE7: DRAIN7:PFET1.2, DRAIN8:W1.1, F7.R1, F7.R2, RC7.1
SENSE8: DRAIN8:PFET1.2, DRAIN9:W1.1, F8.R1, F8.R2, RC8.1
SENSE9: DRAIN9:PFET1.2, F9.R1, F9.R2, GLV_CONTROL.4, RC9.1, RC10.1, TO_TOP.1, TO_TOP.2
SHUTDOWN_CIRCUIT: GLV_CONTROL.1, X6.2, X7.2
SSR-: G1.1, GLV_CONTROL.2
SUPPLY: S1.2, SC1.1, T1.2, T1.4
SUPPLY_INTER: GLV_CONTROL.3, S1.1, S2.1
THERMISTOR1: R101.2, U$2.27, X5.2
THERMISTOR2: R102.2, U$2.28, X4.2
THERMISTOR3: R103.2, U$2.29, X3.2
V+: S2.2, SC2.1, U$2.1
V-: C1.2, C2.2, C3.2, C6.2, C7.2, CR0.2, DRAIN1:W1.1, F0.R1, F0.R2, RB2.1, RC0.1, SC1.2, SC2.2, TEST_PORT.3, U$2.30, U$2.31, U$2.43, U$2.44, X3.1, X4.1, X5.1
VREF1: C2.1, U$2.35
VREF2: C1.1, R101.1, R102.1, R103.1, U$2.34
VREG: C3.1, T1.3, U$2.36, U$2.37, U$2.40
